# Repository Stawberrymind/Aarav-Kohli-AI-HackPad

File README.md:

# Aarav Kohli AI HackPad

This is my open heart AI Hackpad!

Inspiration
I wanted to create a macropad that allowed me to open AI applications I use daily. I created a macropad using 4 switches, 1 rp2040, and 6 leds and 1 rotary encoder. I also love open-heart automatic watches as they show whats really inside, so I went the bold choice of not having a top plate on my keyboard.

Challenges
This was my first time ever using KiCad or Fusion360, I spent a solid day learning these programmes and their fundamentals. I then worked on it and as i kept encountering issues while routing or while exporting, google helped me out along with the KiKad discord community. It was truly a beautiful experience and has helped me dwell deeper into the world of PCB design and CAD design.

Specifications
BOM:

4x Cherry MX Switches
6x SK6812 MINI Leds
1x XIAO RP2040
4x Blank DSA Keycaps
1x Rotary Encoder
Others:

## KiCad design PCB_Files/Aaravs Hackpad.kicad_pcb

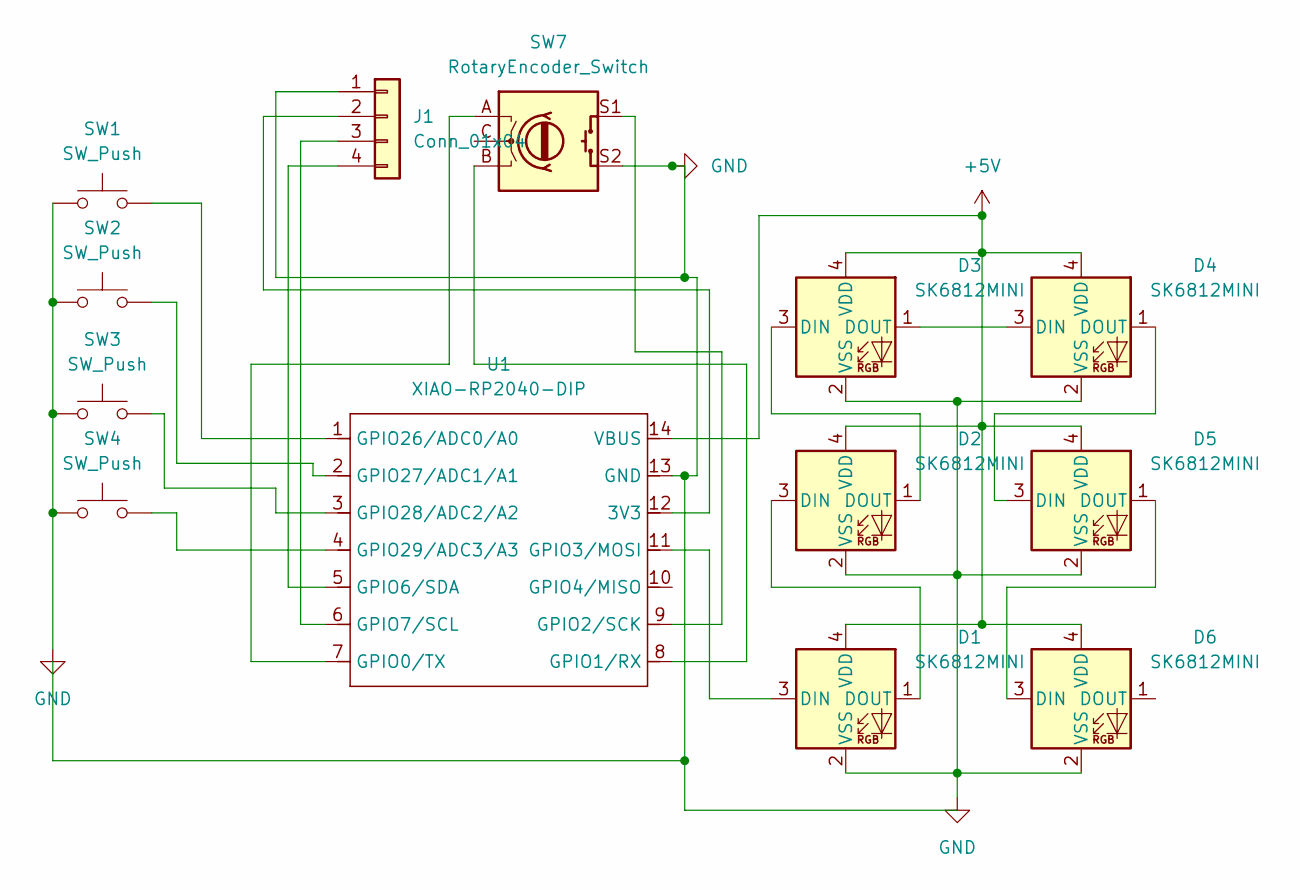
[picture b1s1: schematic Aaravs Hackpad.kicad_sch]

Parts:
D1, D2, D3, D4, D5, D6: SK6812MINI; LED_SK6812MINI_PLCC4_3.5x3.5mm_P1.75mm
J1: Conn_01x04; PinHeader_1x04_P2.54mm_Vertical
SW1, SW2, SW3, SW4: SW_Push; SW_Cherry_MX_1.00u_PCB
SW7: RotaryEncoder_Switch; RotaryEncoder_Alps_EC11E-Switch_Vertical_H20mm_CircularMoun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
U1: XIAO-RP2040-DIP; XIAO-RP2040-SMD

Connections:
+5V: D1.4 (VDD), D2.4 (VDD), D3.4 (VDD), D4.4 (VDD), D5.4 (VDD), D6.4 (VDD), U1.14 (VBUS)
GND: D1.2 (VSS), D2.2 (VSS), D3.2 (VSS), D4.2 (VSS), D5.2 (VSS), D6.2 (VSS), J1.1 (GND), SW1.1, SW2.1, SW3.1, SW4.1, SW7.S2, U1.13 (GND)
unnamed: D1.3 (DIN), U1.11 (GPIO3/MOSI)
unnamed: D1.1 (DOUT), D2.3 (DIN)
unnamed: D2.1 (DOUT), D3.3 (DIN)
unnamed: D3.1 (DOUT), D4.3 (DIN)
unnamed: D4.1 (DOUT), D5.3 (DIN)
unnamed: D5.1 (DOUT), D6.3 (DIN)
unnamed: J1.3 (SCL), U1.6 (GPIO7/SCL)
unnamed: J1.4 (SDA), U1.5 (GPIO6/SDA)
unnamed: J1.2 (VCC), U1.12 (3V3)
unnamed: SW7.A, U1.7 (GPIO0/TX)
unnamed: SW7.B, U1.8 (GPIO1/RX)
unnamed: SW7.S1, U1.9 (GPIO2/SCK)
unnamed: SW1.2, U1.1 (GPIO26/ADC0/A0)
unnamed: SW2.2, U1.2 (GPIO27/ADC1/A1)
unnamed: SW3.2, U1.3 (GPIO28/ADC2/A2)
unnamed: SW4.2, U1.4 (GPIO29/ADC3/A3)

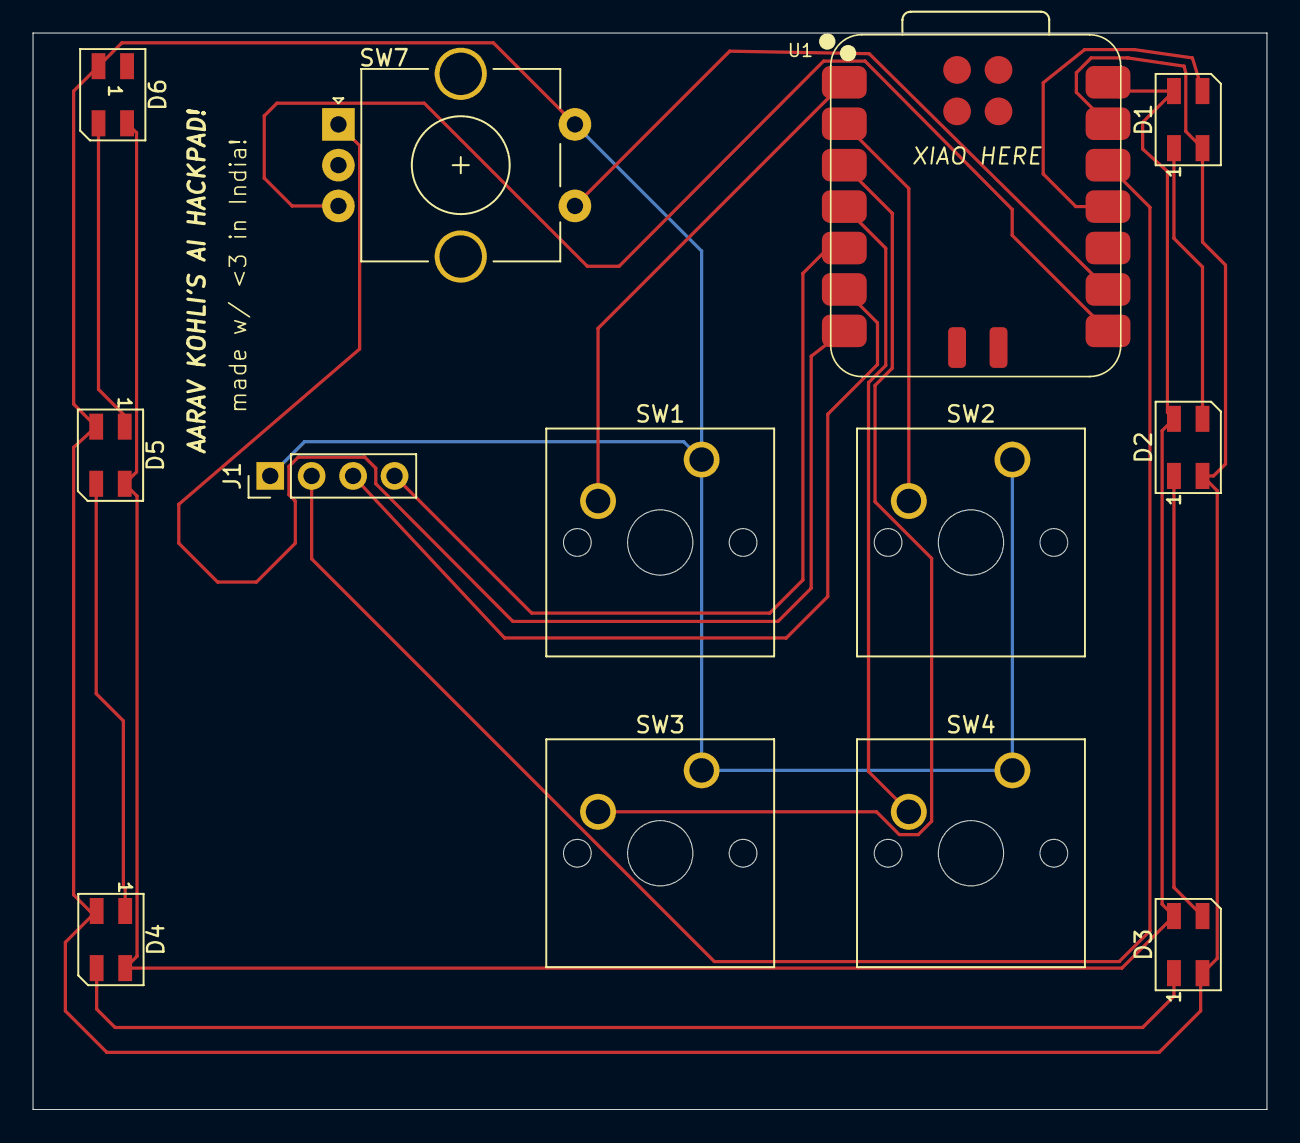
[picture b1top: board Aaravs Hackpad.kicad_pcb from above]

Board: 2 copper layers, 75.6 x 66.0 mm, 13 parts (0 on the bottom side), 18 nets.

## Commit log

2025-12-04 Open-Heart AI Hackpad
2025-12-07 Create Aarav Kohli's AI HackPad Base-STEP.step
    Added base file as STEP
2026-01-30 libraries
    thonny libraries for updated ahk files
